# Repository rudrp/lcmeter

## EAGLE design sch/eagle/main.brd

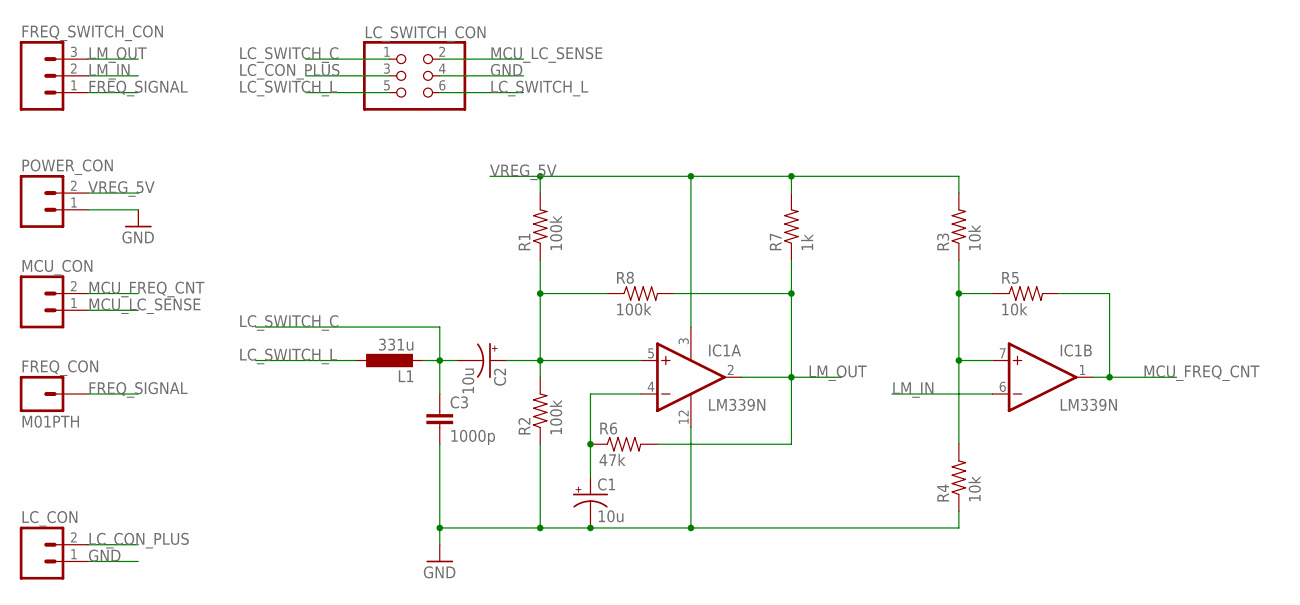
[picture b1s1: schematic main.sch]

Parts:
C1, C2: 10u; CPOL-RADIAL-100UF-25V
C3: 1000p; CAP-PTH-SMALL-KIT
FREQ_CON: M01PTH; 1X01
FREQ_SWITCH_CON: M03PTH; 1X03
IC1: LM339N; DIL14
L1: 331u; 0207/10
LC_CON: M02PTH; 1X02
LC_SWITCH_CON: PINHD-2X3; 2X03
MCU_CON: M02PTH; 1X02
POWER_CON: M02PTH; 1X02
R1, R2, R8: 100k; AXIAL-0.4
R3, R4, R5: 10k; AXIAL-0.4
R6: 47k; AXIAL-0.4
R7: 1k; AXIAL-0.4

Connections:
FREQ_SIGNAL: FREQ_CON.1, FREQ_SWITCH_CON.1
GND: C1.2 (-), C3.2, IC1.12 (GND), LC_CON.1, LC_SWITCH_CON.4, POWER_CON.1, R2.P$1 (1), R4.P$1 (1)
LC_CON_PLUS: LC_CON.2, LC_SWITCH_CON.3
LC_SWITCH_C: C2.2 (-), C3.1, L1.2, LC_SWITCH_CON.1
LC_SWITCH_L: L1.1, LC_SWITCH_CON.5, LC_SWITCH_CON.6
LM_IN: FREQ_SWITCH_CON.2, IC1.6 (-IN)
LM_OUT: FREQ_SWITCH_CON.3, IC1.2 (OUT), R6.P$2 (2), R7.P$1 (1), R8.P$2 (2)
MCU_FREQ_CNT: IC1.1 (OUT), MCU_CON.2, R5.P$2 (2)
MCU_LC_SENSE: LC_SWITCH_CON.2, MCU_CON.1
unnamed: C2.1 (+), IC1.5 (+IN), R1.P$1 (1), R2.P$2 (2), R8.P$1 (1)
unnamed: C1.1 (+), IC1.4 (-IN), R6.P$1 (1)
unnamed: IC1.7 (+IN), R3.P$1 (1), R4.P$2 (2), R5.P$1 (1)
VREG_5V: IC1.3 (V+), POWER_CON.2, R1.P$2 (2), R3.P$2 (2), R7.P$2 (2)

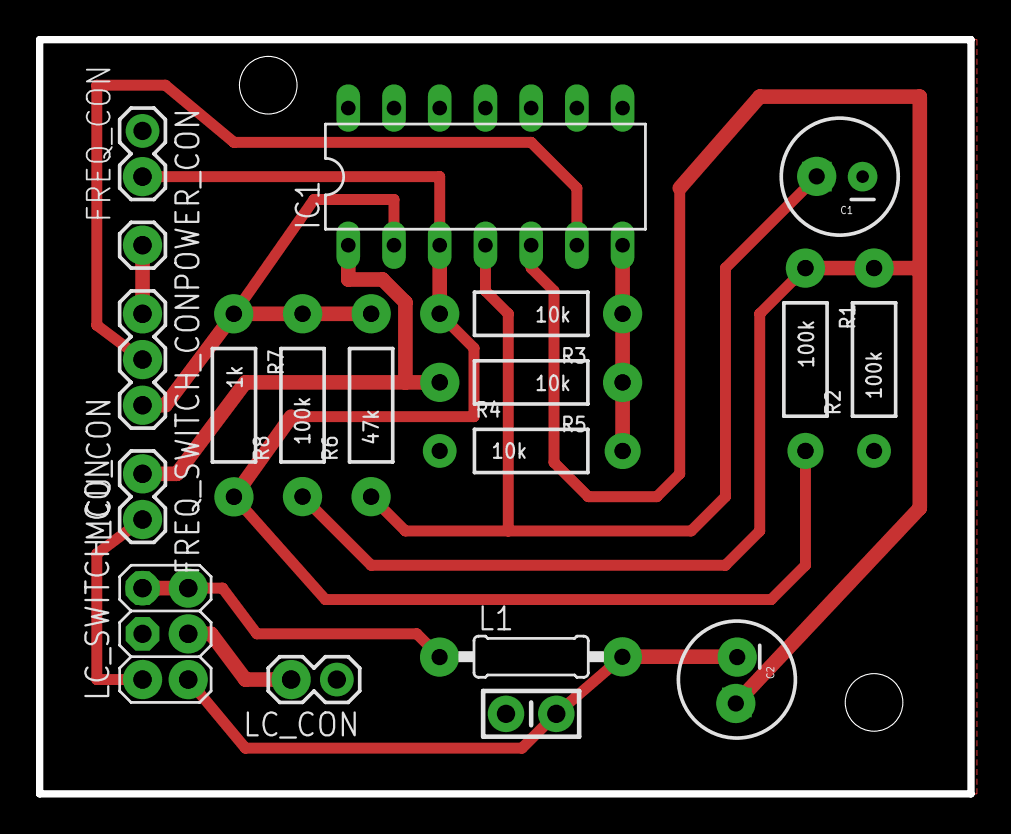
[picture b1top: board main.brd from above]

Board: 2 copper layers, 51.7 x 41.9 mm, 19 parts (0 on the bottom side), 13 nets.

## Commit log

2012-09-19 [ add ] doc/notes
2012-09-19 [ add ] sch/eagle/main.sch
2012-09-19 [ update ] add missing power connections to lm339
2012-09-19 [ add ] dl/kwong/LCFrequencyMeter.pde
2012-09-19 [ update ] doc/notes
2012-09-20 [ add ] src
2012-09-20 [ move ] src to src/atmega328p
2012-09-20 [ update ] add LCD code
2012-09-20 [ update ] comments
2012-09-20 [ update ] correct computation. TODO: calibration mode
2012-09-20 [ update ] calibration mode
2012-09-20 [ update ] doc/notes, calibration section
2012-09-20 [ update ] eagle, mcu_con
2012-09-21 [ update ] eagle, switch connectors
2012-09-21 [ add ] eagle, board routed. to refine.
2012-09-21 [ add ] eagle, board routing refined, wider tracks.
2012-09-21 [ update ] eagle, larger vias
2012-09-21 [ add ] eagle, main.png
2012-09-21 [ update ] reduce some vias to allow ground plane connection
2012-09-22 [ add ] pic/scaled
2012-09-22 [ add ] pic/scaled, LCD
2012-09-22 [ update ] enable CONFIG_LCD. dont update display if x did not change.
2012-09-24 [ update ] print frequency, disable UART
2012-09-25 [ add ] ltspice/main.asc

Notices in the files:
parts and their libraries:
SparkFun: Licensing: CC v3.0 Share-Alike You are welcome to use this library for commercial purposes.
